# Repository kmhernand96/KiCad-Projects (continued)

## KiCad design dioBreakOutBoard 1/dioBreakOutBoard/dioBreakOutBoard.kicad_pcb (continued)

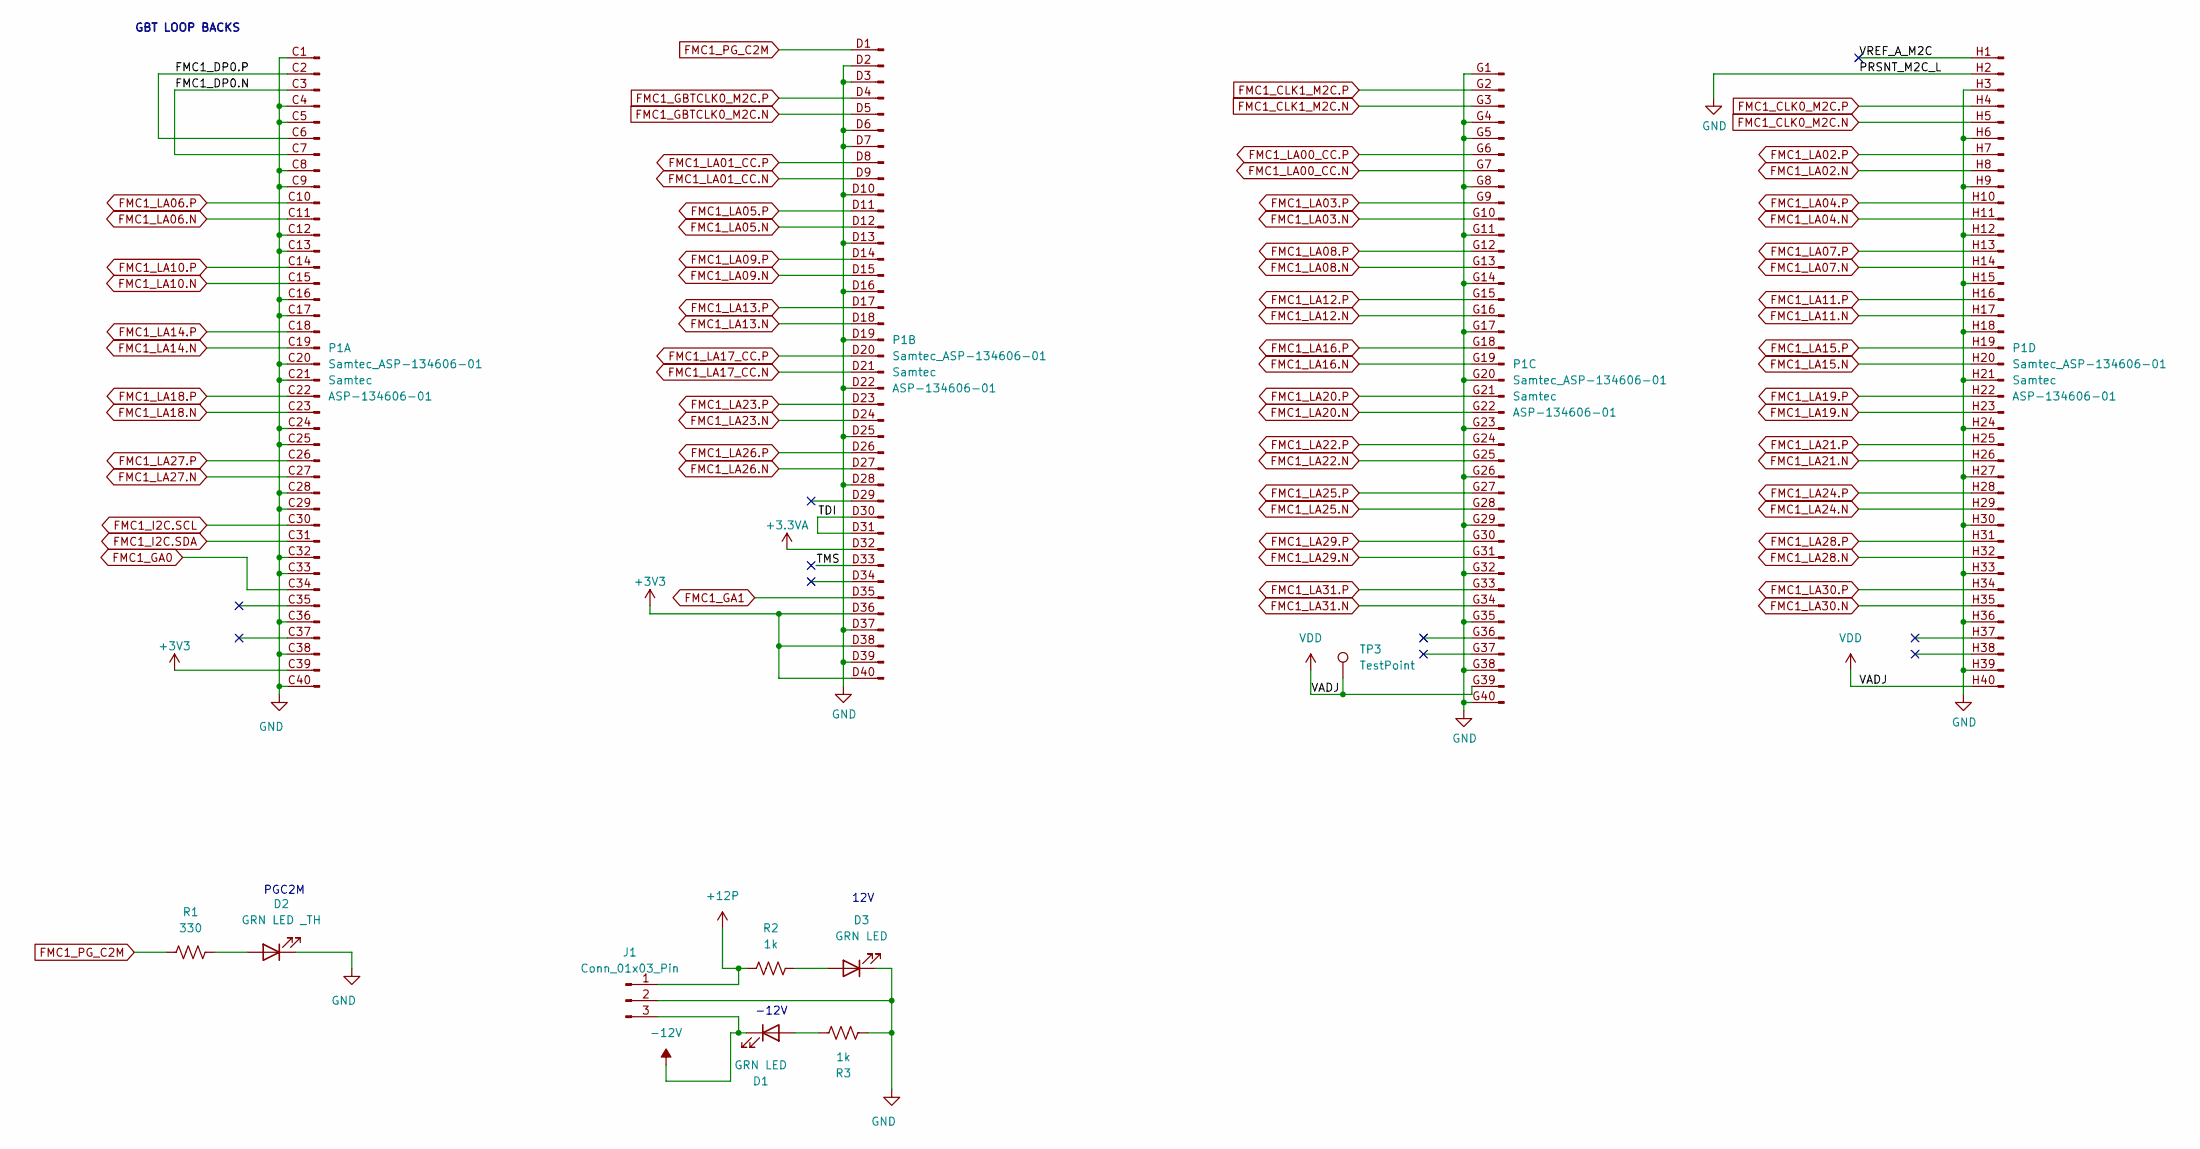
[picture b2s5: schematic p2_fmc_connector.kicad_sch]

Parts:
D1, D3: GRN LED; LED_0603_1608Metric; MFG_PN SML-E12P8WT86
D2: GRN LED _TH; LED_WP934CB&slash_GD_KNB; MFG_PN WP934CB/GD
J1: Conn_01x03_Pin; TE_826576-3_1x03_P3.96mm_Vertical; MFG_PN 0026605030
P1: Samtec_ASP-134606-01; Samtec_FMC_ASP-134606-01_4x40_P1.27mm_Vertical; MFG_PN ASP-134606-01
R1: 330; R_0603_1608Metric; MFG_PN CRCW0603332RFK
R2, R3: 1k; R_0603_1608Metric_Pad0.98x0.95mm_HandSolder; MFG_PN CRCW06031K00FK
TP3: TestPoint; TP_5011series; MFG_PN CRCW0603100KFKEA

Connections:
+3.3VA: P1.D32 (Pin_32); also elsewhere on the board
+3V3: P1.C39 (Pin_39), P1.D36 (Pin_36), P1.D38 (Pin_38), P1.D40 (Pin_40); also elsewhere on the board
+12P: J1.1, R2.1
-12V: D1.1 (K), J1.3
/P2 LPC FMC Connector/FMC1_DP0.N: P1.C3 (Pin_3), P1.C7 (Pin_7)
/P2 LPC FMC Connector/FMC1_DP0.P: P1.C2 (Pin_2), P1.C6 (Pin_6)
/P2 LPC FMC Connector/TDI: P1.D30 (Pin_30), P1.D31 (Pin_31)
/P2 LPC FMC Connector/TMS: P1.D33 (Pin_33)
/P2 LPC FMC Connector/VREF_A_M2C: P1.H1 (Pin_1)
FMC1_CLK0_M2C.N: P1.H5 (Pin_5)
FMC1_CLK0_M2C.P: P1.H4 (Pin_4)
FMC1_CLK1_M2C.N: P1.G3 (Pin_3)
FMC1_CLK1_M2C.P: P1.G2 (Pin_2)
FMC1_GA0: P1.C34 (Pin_34)
FMC1_GA1: P1.D35 (Pin_35)
FMC1_GBTCLK0_M2C.N: P1.D5 (Pin_5)
FMC1_GBTCLK0_M2C.P: P1.D4 (Pin_4)
FMC1_I2C.SCL: P1.C30 (Pin_30)
FMC1_I2C.SDA: P1.C31 (Pin_31)
FMC1_LA00_CC.N: P1.G7 (Pin_7)
FMC1_LA00_CC.P: P1.G6 (Pin_6)
FMC1_LA01_CC.N: P1.D9 (Pin_9)
FMC1_LA01_CC.P: P1.D8 (Pin_8)
FMC1_LA02.N: P1.H8 (Pin_8)
FMC1_LA02.P: P1.H7 (Pin_7)
FMC1_LA03.N: P1.G10 (Pin_10)
FMC1_LA03.P: P1.G9 (Pin_9)
FMC1_LA04.N: P1.H11 (Pin_11)
FMC1_LA04.P: P1.H10 (Pin_10)
FMC1_LA05.N: P1.D12 (Pin_12)
FMC1_LA05.P: P1.D11 (Pin_11)
FMC1_LA06.N: P1.C11 (Pin_11)
FMC1_LA06.P: P1.C10 (Pin_10); also elsewhere on the board
FMC1_LA07.N: P1.H14 (Pin_14)
FMC1_LA07.P: P1.H13 (Pin_13)
FMC1_LA08.N: P1.G13 (Pin_13)
FMC1_LA08.P: P1.G12 (Pin_12)
FMC1_LA09.N: P1.D15 (Pin_15)
FMC1_LA09.P: P1.D14 (Pin_14)
FMC1_LA10.N: P1.C15 (Pin_15); also elsewhere on the board
FMC1_LA10.P: P1.C14 (Pin_14)
FMC1_LA11.N: P1.H17 (Pin_17)
FMC1_LA11.P: P1.H16 (Pin_16)
FMC1_LA12.N: P1.G16 (Pin_16)
FMC1_LA12.P: P1.G15 (Pin_15)
FMC1_LA13.N: P1.D18 (Pin_18)
FMC1_LA13.P: P1.D17 (Pin_17)
FMC1_LA14.N: P1.C19 (Pin_19)
FMC1_LA14.P: P1.C18 (Pin_18)
FMC1_LA15.N: P1.H20 (Pin_20)
FMC1_LA15.P: P1.H19 (Pin_19)
FMC1_LA16.N: P1.G19 (Pin_19)
FMC1_LA16.P: P1.G18 (Pin_18)
FMC1_LA17_CC.N: P1.D21 (Pin_21)
FMC1_LA17_CC.P: P1.D20 (Pin_20)
FMC1_LA18.N: P1.C23 (Pin_23); also elsewhere on the board
FMC1_LA18.P: P1.C22 (Pin_22); also elsewhere on the board
FMC1_LA19.N: P1.H23 (Pin_23)
FMC1_LA19.P: P1.H22 (Pin_22)
FMC1_LA20.N: P1.G22 (Pin_22)
FMC1_LA20.P: P1.G21 (Pin_21)
FMC1_LA21.N: P1.H26 (Pin_26)
FMC1_LA21.P: P1.H25 (Pin_25); also elsewhere on the board
FMC1_LA22.N: P1.G25 (Pin_25)
FMC1_LA22.P: P1.G24 (Pin_24)
FMC1_LA23.N: P1.D24 (Pin_24)
FMC1_LA23.P: P1.D23 (Pin_23)
FMC1_LA24.N: P1.H29 (Pin_29); also elsewhere on the board
FMC1_LA24.P: P1.H28 (Pin_28)
FMC1_LA25.N: P1.G28 (Pin_28)
FMC1_LA25.P: P1.G27 (Pin_27)
FMC1_LA26.N: P1.D27 (Pin_27)
FMC1_LA26.P: P1.D26 (Pin_26)
FMC1_LA27.N: P1.C27 (Pin_27)
FMC1_LA27.P: P1.C26 (Pin_26)
FMC1_LA28.N: P1.H32 (Pin_32)
FMC1_LA28.P: P1.H31 (Pin_31)
FMC1_LA29.N: P1.G31 (Pin_31)
FMC1_LA29.P: P1.G30 (Pin_30)
FMC1_LA30.N: P1.H35 (Pin_35); also elsewhere on the board
FMC1_LA30.P: P1.H34 (Pin_34); also elsewhere on the board
FMC1_LA31.N: P1.G34 (Pin_34)
FMC1_LA31.P: P1.G33 (Pin_33)
FMC1_PG_C2M: P1.D1 (Pin_1), R1.1
GND: D2.1 (K), D3.1 (K), J1.2, P1.C1 (Pin_1), P1.C4 (Pin_4), P1.C5 (Pin_5), P1.C8 (Pin_8), P1.C9 (Pin_9), P1.C12 (Pin_12), P1.C13 (Pin_13), P1.C16 (Pin_16), P1.C17 (Pin_17), P1.C20 (Pin_20), P1.C21 (Pin_21), P1.C24 (Pin_24), P1.C25 (Pin_25), P1.C28 (Pin_28), P1.C29 (Pin_29), P1.C32 (Pin_32), P1.C33 (Pin_33), P1.C36 (Pin_36), P1.C38 (Pin_38), P1.C40 (Pin_40), P1.D2 (Pin_2), P1.D3 (Pin_3), P1.D6 (Pin_6), P1.D7 (Pin_7), P1.D10 (Pin_10), P1.D13 (Pin_13), P1.D16 (Pin_16), P1.D19 (Pin_19), P1.D22 (Pin_22), P1.D25 (Pin_25), P1.D28 (Pin_28), P1.D37 (Pin_37), P1.D39 (Pin_39), P1.G1 (Pin_1), P1.G4 (Pin_4), P1.G5 (Pin_5), P1.G8 (Pin_8), P1.G11 (Pin_11), P1.G14 (Pin_14), P1.G17 (Pin_17), P1.G20 (Pin_20), P1.G23 (Pin_23), P1.G26 (Pin_26), P1.G29 (Pin_29), P1.G32 (Pin_32), P1.G35 (Pin_35), P1.G38 (Pin_38), P1.G40 (Pin_40), P1.H2 (Pin_2), P1.H3 (Pin_3), P1.H6 (Pin_6), P1.H9 (Pin_9), P1.H12 (Pin_12), P1.H15 (Pin_15), P1.H18 (Pin_18), P1.H21 (Pin_21), P1.H24 (Pin_24), P1.H27 (Pin_27), P1.H30 (Pin_30), P1.H33 (Pin_33), P1.H36 (Pin_36), P1.H39 (Pin_39), R3.1; also elsewhere on the board
unnamed: D1.2 (A), R3.2
unnamed: D2.2 (A), R1.2
unnamed: D3.2 (A), R2.2
VDD: P1.G39 (Pin_39), P1.H40 (Pin_40), TP3.1

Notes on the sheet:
GBT LOOP BACKS
-12V
12V
PGC2M

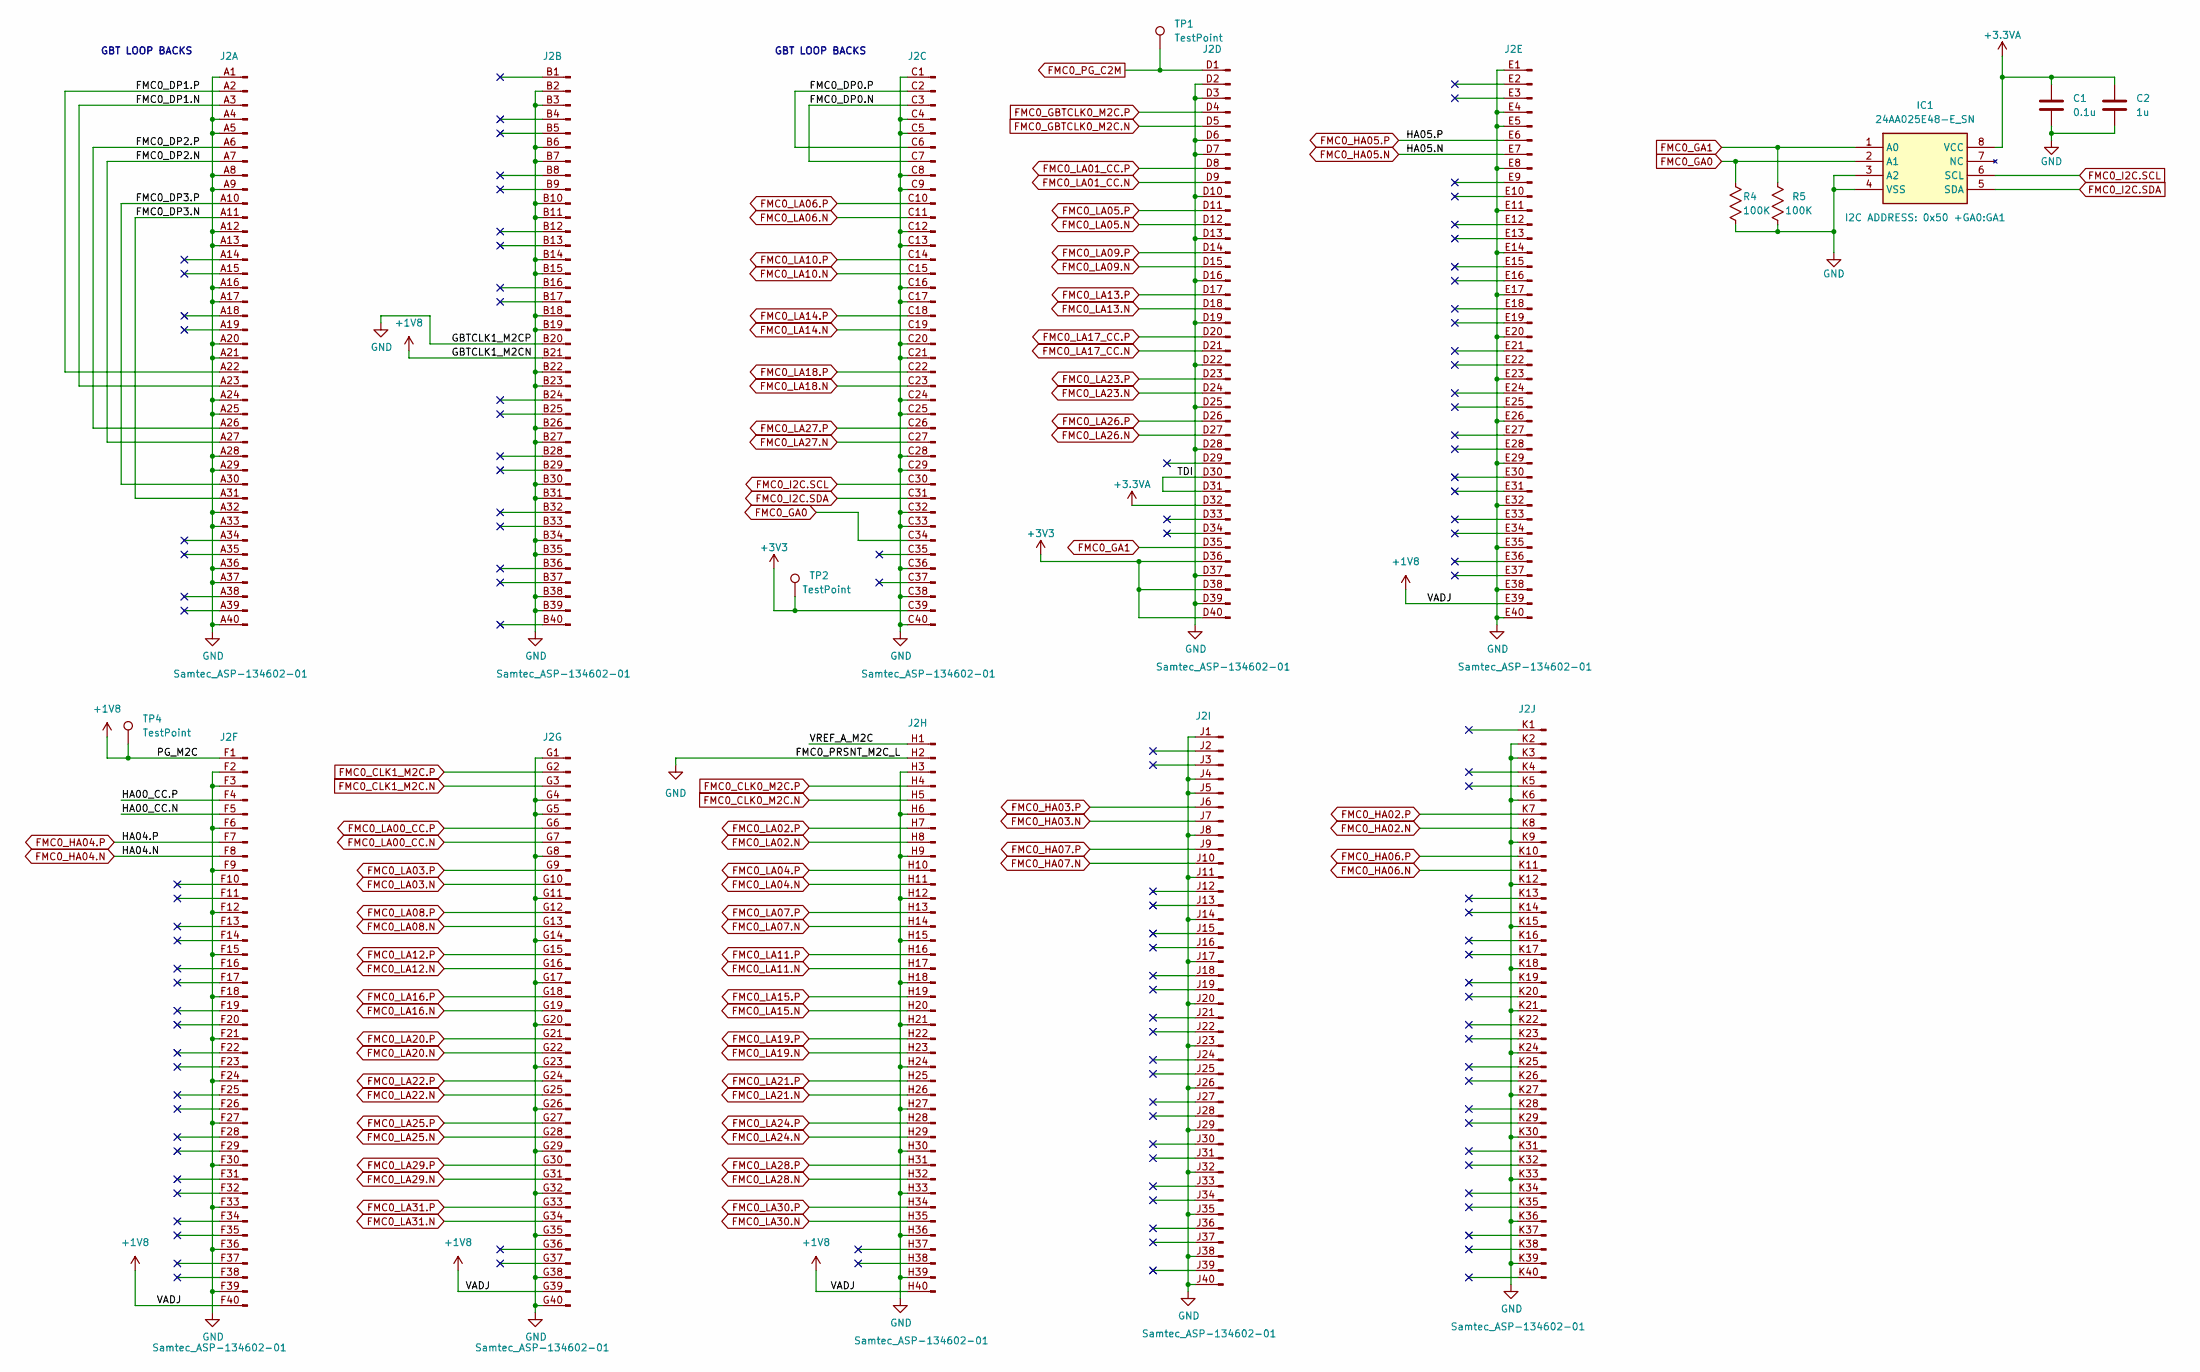
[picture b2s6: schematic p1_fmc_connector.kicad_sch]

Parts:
C1: 0.1u; C_0603_1608Metric; MFG_PN TMK107BJ104KA-T
C2: 1u; C_0805_2012Metric_Pad1.18x1.45mm_HandSolder; MFG_PN TMK212B7105KG-T
IC1: 24AA025E48-E_SN; SOIC-8_5.23x5.23mm_P1.27mm; Mouser Part Number 579-24AA025E48-E/SN
J2: Samtec_ASP-134602-01; Samtec_FMC_ASP-134602-01_10x40_P1.27mm_Vertical; MFG_PN ASP-134602-01
R4, R5: 100K; R_0603_1608Metric; MFG_PN Empty
TP1, TP2, TP4: TestPoint; TP_5011series; MFG_PN CRCW0603100KFKEA

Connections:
+1V8: J2.B21 (Pin_21), J2.E39 (Pin_39), J2.F1 (Pin_1), J2.F40 (Pin_40), J2.G39 (Pin_39), J2.H40 (Pin_40), TP4.1; also elsewhere on the board
+3.3VA: C1.2, C2.2, IC1.8 (VCC), J2.D32 (Pin_32); also elsewhere on the board
+3V3: J2.C39 (Pin_39), J2.D36 (Pin_36), J2.D38 (Pin_38), J2.D40 (Pin_40), TP2.1; also elsewhere on the board
/P1 HPC FMC Connector/FMC0_DP0.N: J2.C3 (Pin_3), J2.C7 (Pin_7)
/P1 HPC FMC Connector/FMC0_DP0.P: J2.C2 (Pin_2), J2.C6 (Pin_6)
/P1 HPC FMC Connector/FMC0_DP1.N: J2.A3 (Pin_3), J2.A23 (Pin_23)
/P1 HPC FMC Connector/FMC0_DP1.P: J2.A2 (Pin_2), J2.A22 (Pin_22)
/P1 HPC FMC Connector/FMC0_DP2.N: J2.A7 (Pin_7), J2.A27 (Pin_27)
/P1 HPC FMC Connector/FMC0_DP2.P: J2.A6 (Pin_6), J2.A26 (Pin_26)
/P1 HPC FMC Connector/FMC0_DP3.N: J2.A11 (Pin_11), J2.A31 (Pin_31)
/P1 HPC FMC Connector/FMC0_DP3.P: J2.A10 (Pin_10), J2.A30 (Pin_30)
/P1 HPC FMC Connector/HA00_CC.N: J2.F5 (Pin_5)
/P1 HPC FMC Connector/HA00_CC.P: J2.F4 (Pin_4)
/P1 HPC FMC Connector/TDI: J2.D30 (Pin_30), J2.D31 (Pin_31)
/P1 HPC FMC Connector/VREF_A_M2C: J2.H1 (Pin_1)
FMC0_CLK0_M2C.N: J2.H5 (Pin_5)
FMC0_CLK0_M2C.P: J2.H4 (Pin_4)
FMC0_CLK1_M2C.N: J2.G3 (Pin_3)
FMC0_CLK1_M2C.P: J2.G2 (Pin_2)
FMC0_GA0: IC1.2 (A1), J2.C34 (Pin_34), R4.1
FMC0_GA1: IC1.1 (A0), J2.D35 (Pin_35), R5.1
FMC0_GBTCLK0_M2C.N: J2.D5 (Pin_5)
FMC0_GBTCLK0_M2C.P: J2.D4 (Pin_4)
FMC0_HA02.N: J2.K8 (Pin_8)
FMC0_HA02.P: J2.K7 (Pin_7)
FMC0_HA03.N: J2.J7 (Pin_7)
FMC0_HA03.P: J2.J6 (Pin_6)
FMC0_HA04.N: J2.F8 (Pin_8)
FMC0_HA04.P: J2.F7 (Pin_7)
FMC0_HA05.N: J2.E7 (Pin_7)
FMC0_HA05.P: J2.E6 (Pin_6)
FMC0_HA06.N: J2.K11 (Pin_11)
FMC0_HA06.P: J2.K10 (Pin_10)
FMC0_HA07.N: J2.J10 (Pin_10)
FMC0_HA07.P: J2.J9 (Pin_9)
FMC0_I2C.SCL: IC1.6 (SCL), J2.C30 (Pin_30)
FMC0_I2C.SDA: IC1.5 (SDA), J2.C31 (Pin_31)
FMC0_LA00_CC.N: J2.G7 (Pin_7); also elsewhere on the board
FMC0_LA00_CC.P: J2.G6 (Pin_6); also elsewhere on the board
FMC0_LA01_CC.N: J2.D9 (Pin_9); also elsewhere on the board
FMC0_LA01_CC.P: J2.D8 (Pin_8); also elsewhere on the board
FMC0_LA02.N: J2.H8 (Pin_8); also elsewhere on the board
FMC0_LA02.P: J2.H7 (Pin_7); also elsewhere on the board
FMC0_LA03.N: J2.G10 (Pin_10); also elsewhere on the board
FMC0_LA03.P: J2.G9 (Pin_9); also elsewhere on the board
FMC0_LA04.N: J2.H11 (Pin_11); also elsewhere on the board
FMC0_LA04.P: J2.H10 (Pin_10); also elsewhere on the board
FMC0_LA05.N: J2.D12 (Pin_12); also elsewhere on the board
FMC0_LA05.P: J2.D11 (Pin_11); also elsewhere on the board
FMC0_LA06.N: J2.C11 (Pin_11); also elsewhere on the board
FMC0_LA06.P: J2.C10 (Pin_10); also elsewhere on the board
FMC0_LA07.N: J2.H14 (Pin_14); also elsewhere on the board
FMC0_LA07.P: J2.H13 (Pin_13); also elsewhere on the board
FMC0_LA08.N: J2.G13 (Pin_13); also elsewhere on the board
FMC0_LA08.P: J2.G12 (Pin_12); also elsewhere on the board
FMC0_LA09.N: J2.D15 (Pin_15); also elsewhere on the board
FMC0_LA09.P: J2.D14 (Pin_14); also elsewhere on the board
FMC0_LA10.N: J2.C15 (Pin_15); also elsewhere on the board
FMC0_LA10.P: J2.C14 (Pin_14); also elsewhere on the board
FMC0_LA11.N: J2.H17 (Pin_17); also elsewhere on the board
FMC0_LA11.P: J2.H16 (Pin_16); also elsewhere on the board
FMC0_LA12.N: J2.G16 (Pin_16); also elsewhere on the board
FMC0_LA12.P: J2.G15 (Pin_15); also elsewhere on the board
FMC0_LA13.N: J2.D18 (Pin_18); also elsewhere on the board
FMC0_LA13.P: J2.D17 (Pin_17); also elsewhere on the board
FMC0_LA14.N: J2.C19 (Pin_19); also elsewhere on the board
FMC0_LA14.P: J2.C18 (Pin_18); also elsewhere on the board
FMC0_LA15.N: J2.H20 (Pin_20); also elsewhere on the board
FMC0_LA15.P: J2.H19 (Pin_19); also elsewhere on the board
FMC0_LA16.N: J2.G19 (Pin_19); also elsewhere on the board
FMC0_LA16.P: J2.G18 (Pin_18); also elsewhere on the board
FMC0_LA17_CC.N: J2.D21 (Pin_21); also elsewhere on the board
FMC0_LA17_CC.P: J2.D20 (Pin_20); also elsewhere on the board
FMC0_LA18.N: J2.C23 (Pin_23); also elsewhere on the board
FMC0_LA18.P: J2.C22 (Pin_22); also elsewhere on the board
FMC0_LA19.N: J2.H23 (Pin_23); also elsewhere on the board
FMC0_LA19.P: J2.H22 (Pin_22); also elsewhere on the board
FMC0_LA20.N: J2.G22 (Pin_22); also elsewhere on the board
FMC0_LA20.P: J2.G21 (Pin_21); also elsewhere on the board
FMC0_LA21.N: J2.H26 (Pin_26); also elsewhere on the board
FMC0_LA21.P: J2.H25 (Pin_25); also elsewhere on the board
FMC0_LA22.N: J2.G25 (Pin_25); also elsewhere on the board
FMC0_LA22.P: J2.G24 (Pin_24); also elsewhere on the board
FMC0_LA23.N: J2.D24 (Pin_24); also elsewhere on the board
FMC0_LA23.P: J2.D23 (Pin_23); also elsewhere on the board
FMC0_LA24.N: J2.H29 (Pin_29); also elsewhere on the board
FMC0_LA24.P: J2.H28 (Pin_28); also elsewhere on the board
FMC0_LA25.N: J2.G28 (Pin_28); also elsewhere on the board
FMC0_LA25.P: J2.G27 (Pin_27); also elsewhere on the board
FMC0_LA26.N: J2.D27 (Pin_27); also elsewhere on the board
FMC0_LA26.P: J2.D26 (Pin_26); also elsewhere on the board
FMC0_LA27.N: J2.C27 (Pin_27); also elsewhere on the board
FMC0_LA27.P: J2.C26 (Pin_26); also elsewhere on the board
FMC0_LA28.N: J2.H32 (Pin_32); also elsewhere on the board
FMC0_LA28.P: J2.H31 (Pin_31); also elsewhere on the board
FMC0_LA29.N: J2.G31 (Pin_31); also elsewhere on the board
FMC0_LA29.P: J2.G30 (Pin_30); also elsewhere on the board
FMC0_LA30.N: J2.H35 (Pin_35); also elsewhere on the board
FMC0_LA30.P: J2.H34 (Pin_34); also elsewhere on the board
FMC0_LA31.N: J2.G34 (Pin_34); also elsewhere on the board
FMC0_LA31.P: J2.G33 (Pin_33); also elsewhere on the board
FMC0_PG_C2M: J2.D1 (Pin_1), TP1.1
GND: C1.1, C2.1, IC1.3 (A2), IC1.4 (VSS), J2.A1 (Pin_1), J2.A4 (Pin_4), J2.A5 (Pin_5), J2.A8 (Pin_8), J2.A9 (Pin_9), J2.A12 (Pin_12), J2.A13 (Pin_13), J2.A16 (Pin_16), J2.A17 (Pin_17), J2.A20 (Pin_20), J2.A21 (Pin_21), J2.A24 (Pin_24), J2.A25 (Pin_25), J2.A28 (Pin_28), J2.A29 (Pin_29), J2.A32 (Pin_32), J2.A33 (Pin_33), J2.A36 (Pin_36), J2.A37 (Pin_37), J2.A40 (Pin_40), J2.B2 (Pin_2), J2.B3 (Pin_3), J2.B6 (Pin_6), J2.B7 (Pin_7), J2.B10 (Pin_10), J2.B11 (Pin_11), J2.B14 (Pin_14), J2.B15 (Pin_15), J2.B18 (Pin_18), J2.B19 (Pin_19), J2.B20 (Pin_20), J2.B22 (Pin_22), J2.B23 (Pin_23), J2.B26 (Pin_26), J2.B27 (Pin_27), J2.B30 (Pin_30), J2.B31 (Pin_31), J2.B34 (Pin_34), J2.B35 (Pin_35), J2.B38 (Pin_38), J2.B39 (Pin_39), J2.C1 (Pin_1), J2.C4 (Pin_4), J2.C5 (Pin_5), J2.C8 (Pin_8), J2.C9 (Pin_9), J2.C12 (Pin_12), J2.C13 (Pin_13), J2.C16 (Pin_16), J2.C17 (Pin_17), J2.C20 (Pin_20), J2.C21 (Pin_21), J2.C24 (Pin_24), J2.C25 (Pin_25), J2.C28 (Pin_28), J2.C29 (Pin_29), J2.C32 (Pin_32), J2.C33 (Pin_33), J2.C36 (Pin_36), J2.C38 (Pin_38), J2.C40 (Pin_40), J2.D2 (Pin_2), J2.D3 (Pin_3), J2.D6 (Pin_6), J2.D7 (Pin_7), J2.D10 (Pin_10), J2.D13 (Pin_13), J2.D16 (Pin_16), J2.D19 (Pin_19), J2.D22 (Pin_22), J2.D25 (Pin_25), J2.D28 (Pin_28), J2.D37 (Pin_37), J2.D39 (Pin_39), J2.E1 (Pin_1), J2.E4 (Pin_4), J2.E5 (Pin_5), J2.E8 (Pin_8), J2.E11 (Pin_11), J2.E14 (Pin_14), J2.E17 (Pin_17), J2.E20 (Pin_20), J2.E23 (Pin_23), J2.E26 (Pin_26), J2.E29 (Pin_29), J2.E32 (Pin_32), J2.E35 (Pin_35), J2.E38 (Pin_38), J2.E40 (Pin_40), J2.F2 (Pin_2), J2.F3 (Pin_3), J2.F6 (Pin_6), J2.F9 (Pin_9), J2.F12 (Pin_12), J2.F15 (Pin_15), J2.F18 (Pin_18), J2.F21 (Pin_21), J2.F24 (Pin_24), J2.F27 (Pin_27), J2.F30 (Pin_30), J2.F33 (Pin_33), J2.F36 (Pin_36), J2.F39 (Pin_39), J2.G1 (Pin_1), J2.G4 (Pin_4), J2.G5 (Pin_5), J2.G8 (Pin_8), J2.G11 (Pin_11), J2.G14 (Pin_14), J2.G17 (Pin_17), J2.G20 (Pin_20), J2.G23 (Pin_23), J2.G26 (Pin_26), J2.G29 (Pin_29), J2.G32 (Pin_32), J2.G35 (Pin_35), J2.G38 (Pin_38), J2.G40 (Pin_40), J2.H2 (Pin_2), J2.H3 (Pin_3), J2.H6 (Pin_6), J2.H9 (Pin_9), J2.H12 (Pin_12), J2.H15 (Pin_15), J2.H18 (Pin_18), J2.H21 (Pin_21), J2.H24 (Pin_24), J2.H27 (Pin_27), J2.H30 (Pin_30), J2.H33 (Pin_33), J2.H36 (Pin_36), J2.H39 (Pin_39), J2.J1 (Pin_1), J2.J4 (Pin_4), J2.J5 (Pin_5), J2.J8 (Pin_8), J2.J11 (Pin_11), J2.J14 (Pin_14), J2.J17 (Pin_17), J2.J20 (Pin_20), J2.J23 (Pin_23), J2.J26 (Pin_26), J2.J29 (Pin_29), J2.J32 (Pin_32), J2.J35 (Pin_35), J2.J38 (Pin_38), J2.J40 (Pin_40), J2.K2 (Pin_2), J2.K3 (Pin_3), J2.K6 (Pin_6), J2.K9 (Pin_9), J2.K12 (Pin_12), J2.K15 (Pin_15), J2.K18 (Pin_18), J2.K21 (Pin_21), J2.K24 (Pin_24), J2.K27 (Pin_27), J2.K30 (Pin_30), J2.K33 (Pin_33), J2.K36 (Pin_36), J2.K39 (Pin_39), R4.2, R5.2; also elsewhere on the board

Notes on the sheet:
GBT LOOP BACKS

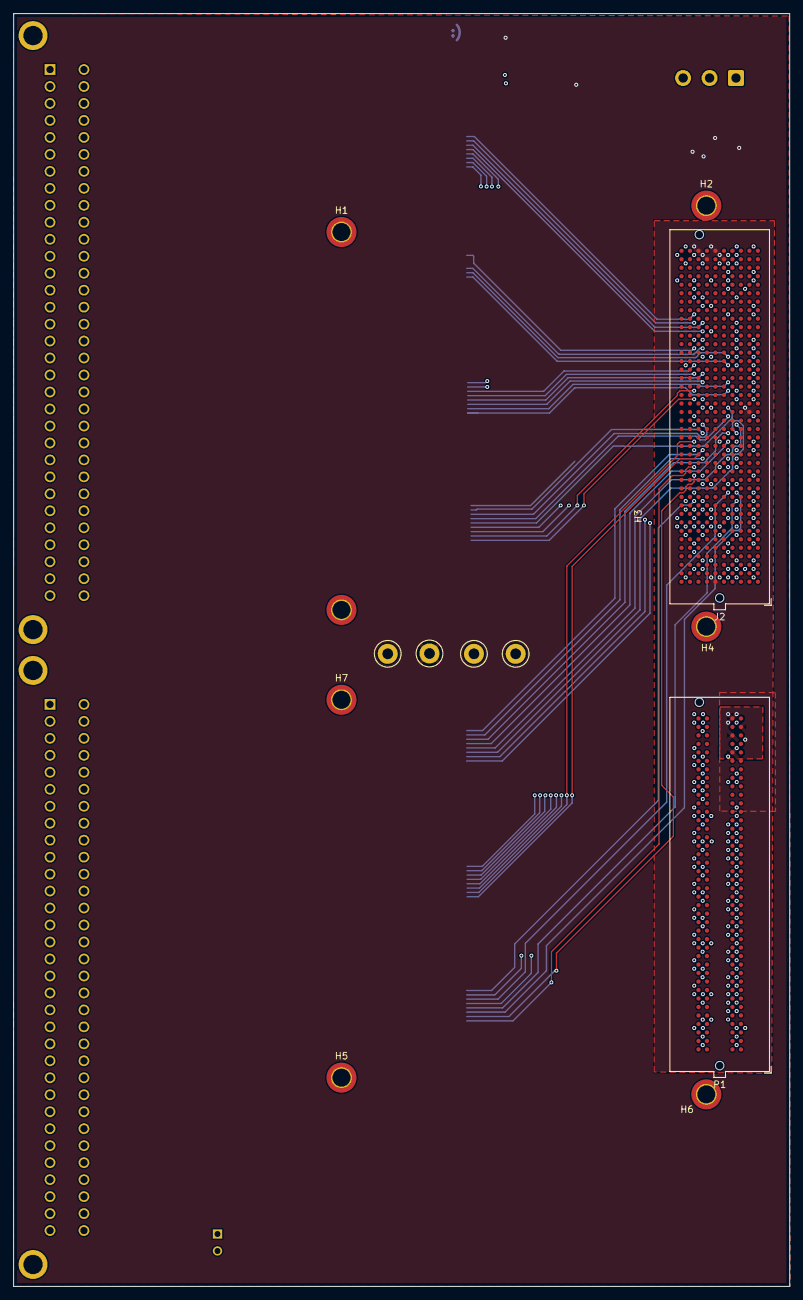
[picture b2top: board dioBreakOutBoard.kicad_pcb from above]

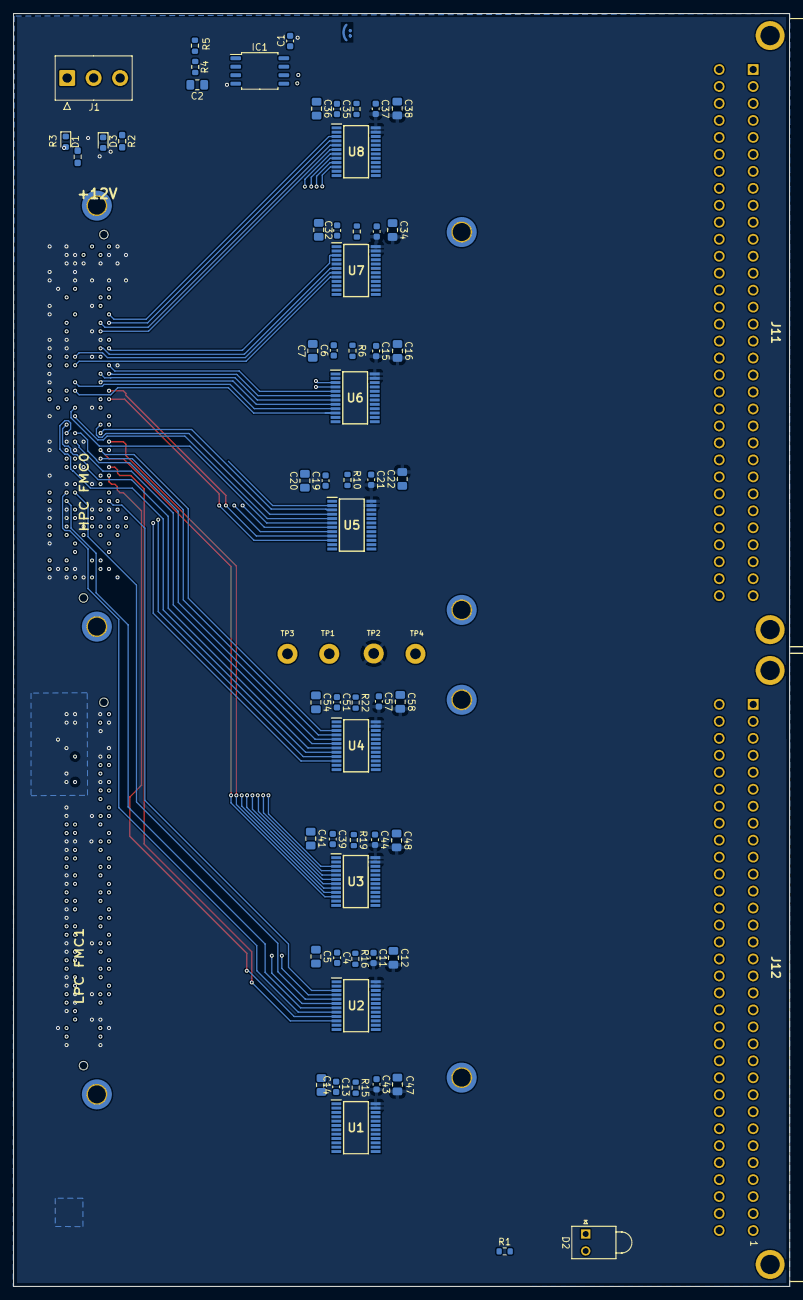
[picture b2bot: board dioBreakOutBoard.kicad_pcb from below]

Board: 4 copper layers, 116.2 x 190.5 mm, 75 parts (62 on the bottom side), 164 nets.

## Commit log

2024-12-11 Added RTX project
2024-12-11 Adding a few libraries for parts from the RTx project, just to get started
2024-12-18 C:\Users\khernandez\KiCad\KiCad-Project
    Preliminary Part Placement
2024-12-18 Changes to Library and Connector Kind
2025-01-02 Changed the voltage regulator to a chunky SOT23 package
2025-01-13 More routing done
2025-02-10 C:\Users\khernandez\KiCad\KiCad-Projects# Please enter the commit message for your changes. Lines starting
2025-03-25 added 2 bit buffers, which replace the previous 8 bit buffers
